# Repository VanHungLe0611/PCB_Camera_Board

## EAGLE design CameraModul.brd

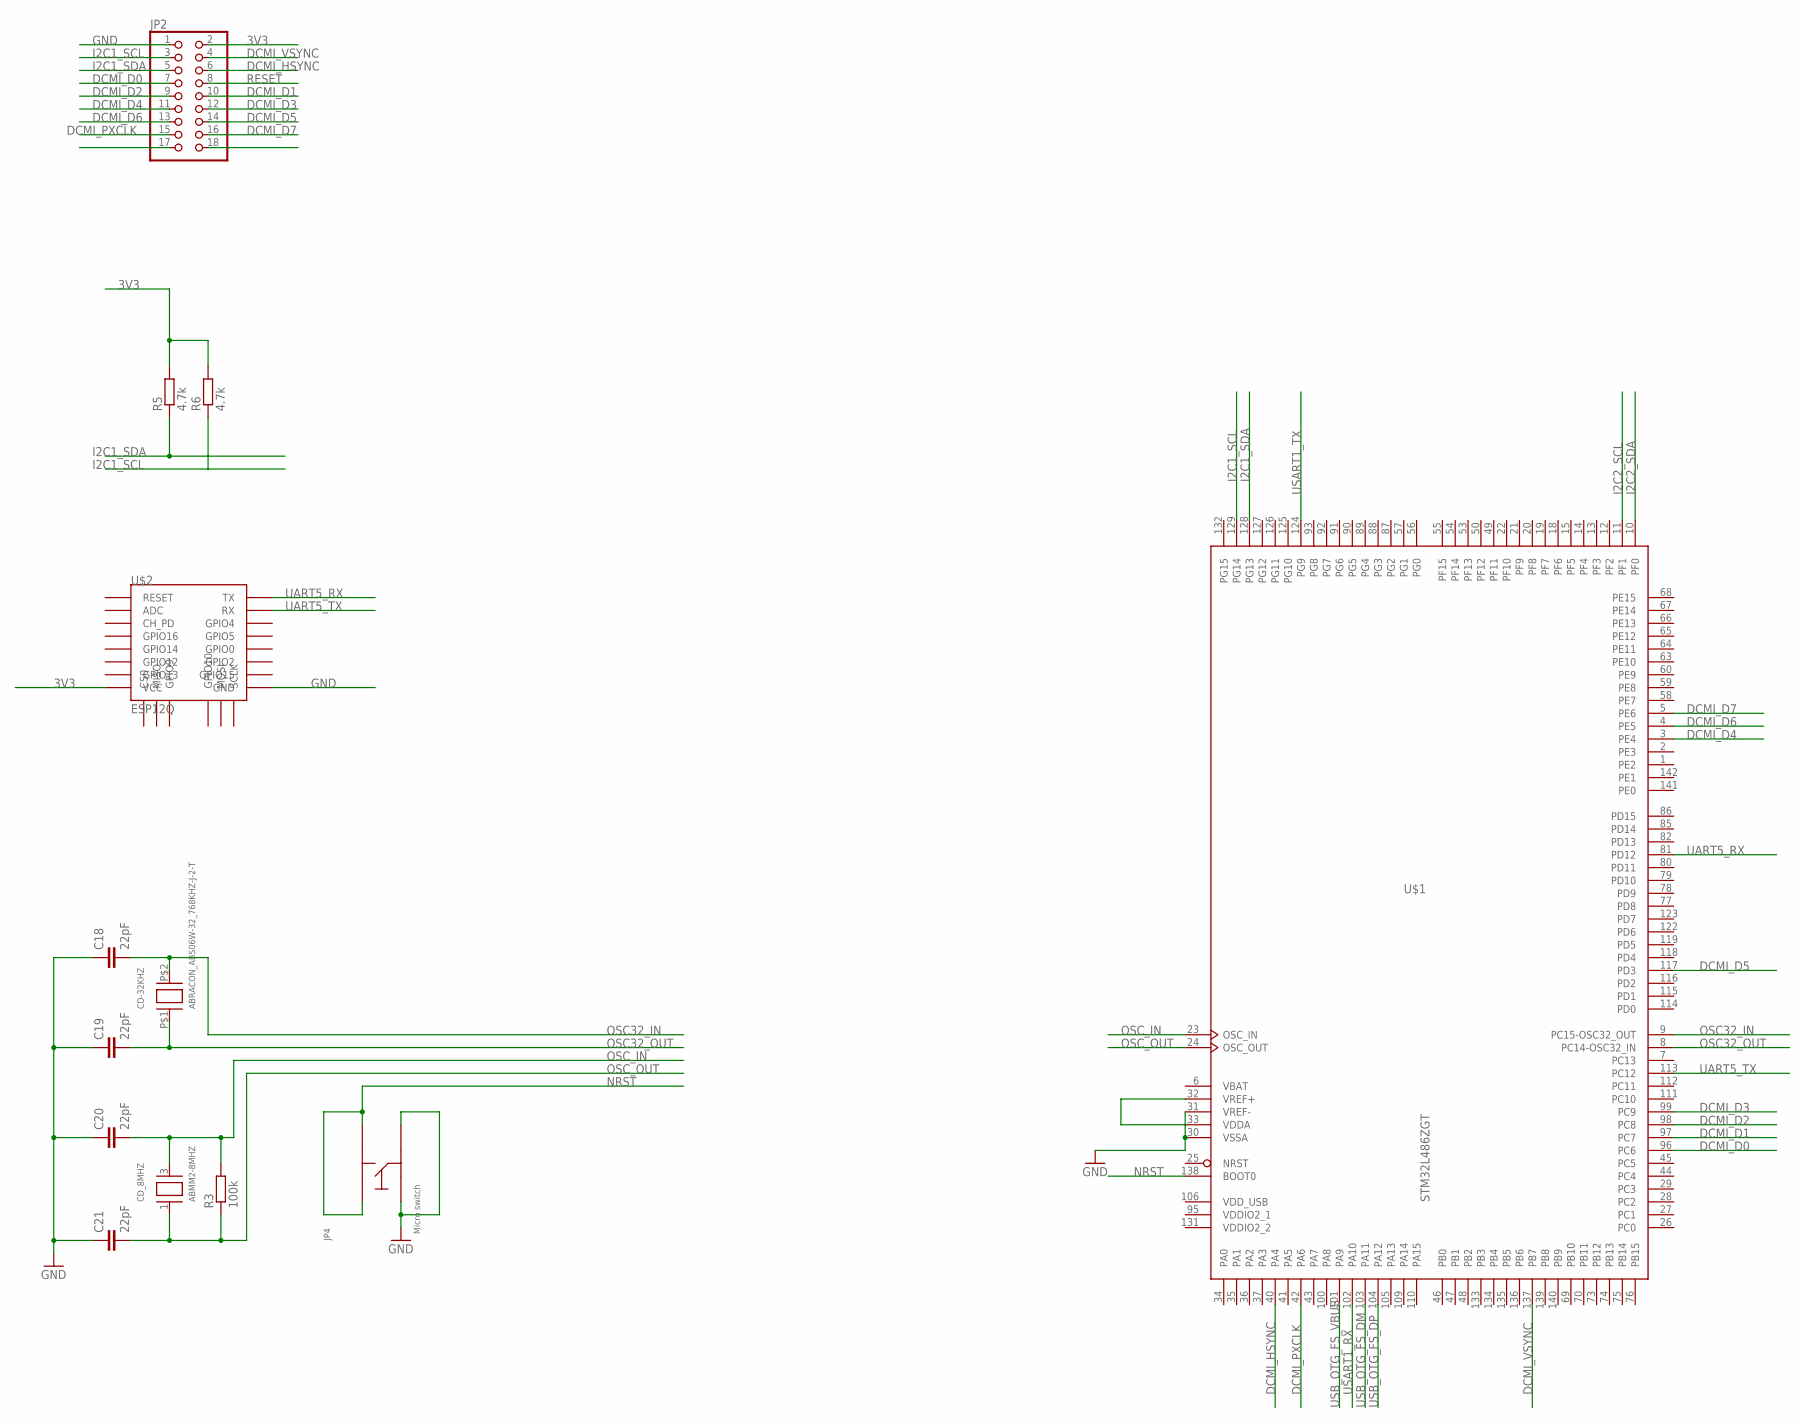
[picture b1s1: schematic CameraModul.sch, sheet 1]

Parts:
C18, C19, C20, C21: 22pF; C0402K
CD-32KHZ: ABRACON_ABS06W-32_768KHZ-J-2-T; 2MM_X_1_2MM
CD_8MHZ: ABMM2-8MHZ; CRYSTAL_ABRACON_6MM_3.6MM
JP2: PINHD-2X9; 2X09
JP4: MICRO_SWITCH_6MM; SKQGADE010
R3: 100k; C0402K
R5, R6: 4.7k; C0402K
U$1: STM32L486ZGT; LQFP144
U$2: ESP12Q

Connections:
3V3: JP2.2, R5.2, R6.2, U$1.32 (VREF+), U$1.33 (VDDA), U$2.VCC; also elsewhere on the board
DCMI_D0: JP2.7, U$1.96 (PC6)
DCMI_D1: JP2.10, U$1.97 (PC7)
DCMI_D2: JP2.9, U$1.98 (PC8)
DCMI_D3: JP2.12, U$1.99 (PC9)
DCMI_D4: JP2.11, U$1.3 (PE4)
DCMI_D5: JP2.14, U$1.117 (PD3)
DCMI_D6: JP2.13, U$1.4 (PE5)
DCMI_D7: JP2.16, U$1.5 (PE6)
DCMI_HSYNC: JP2.6, U$1.40 (PA4)
DCMI_PXCLK: JP2.15, U$1.42 (PA6)
DCMI_VSYNC: JP2.4, U$1.137 (PB7)
GND: C18.1, C19.1, C20.1, C21.1, JP2.1, JP4.P$3, JP4.P$4, U$1.30 (VSSA), U$1.31 (VREF-), U$2.GND; also elsewhere on the board
I2C1_SCL: JP2.3, R6.1, U$1.129 (PG14)
I2C1_SDA: JP2.5, R5.1, U$1.128 (PG13)
I2C2_SCL: U$1.11 (PF1)
I2C2_SDA: U$1.10 (PF0)
NRST: JP4.P$1, JP4.P$2, U$1.138 (BOOT0)
OSC32_IN: C18.2, CD-32KHZ.P$2 (C1), U$1.9 (PC15-OSC32_OUT)
OSC32_OUT: C19.2, CD-32KHZ.P$1 (C0), U$1.8 (PC14-OSC32_IN)
OSC_IN: C20.2, CD_8MHZ.3 (C1), R3.2, U$1.23 (OSC_IN)
OSC_OUT: C21.2, CD_8MHZ.1 (C0), R3.1, U$1.24 (OSC_OUT)
RESET: JP2.8
UART5_RX: U$1.81 (PD12), U$2.TX
UART5_TX: U$1.113 (PC12), U$2.RX
USART1_RX: U$1.102 (PA10); also elsewhere on the board
USART1_TX: U$1.124 (PG9); also elsewhere on the board
USB_OTG_FS_DM: U$1.103 (PA11); also elsewhere on the board
USB_OTG_FS_DP: U$1.104 (PA12); also elsewhere on the board
USB_OTG_FS_VBUS: U$1.101 (PA9); also elsewhere on the board
VBAT: U$1.6 (VBAT); also elsewhere on the board
VDD: U$1.17 (VDD), U$1.39 (VDD), U$1.52 (VDD), U$1.62 (VDD), U$1.72 (VDD), U$1.84 (VDD), U$1.108 (VDD), U$1.121 (VDD), U$1.144 (VDD)
VSS: U$1.16 (VSS), U$1.38 (VSS), U$1.51 (VSS), U$1.61 (VSS), U$1.71 (VSS), U$1.83 (VSS), U$1.94 (VSS), U$1.107 (VSS), U$1.120 (VSS), U$1.130 (VSS), U$1.143 (VSS)

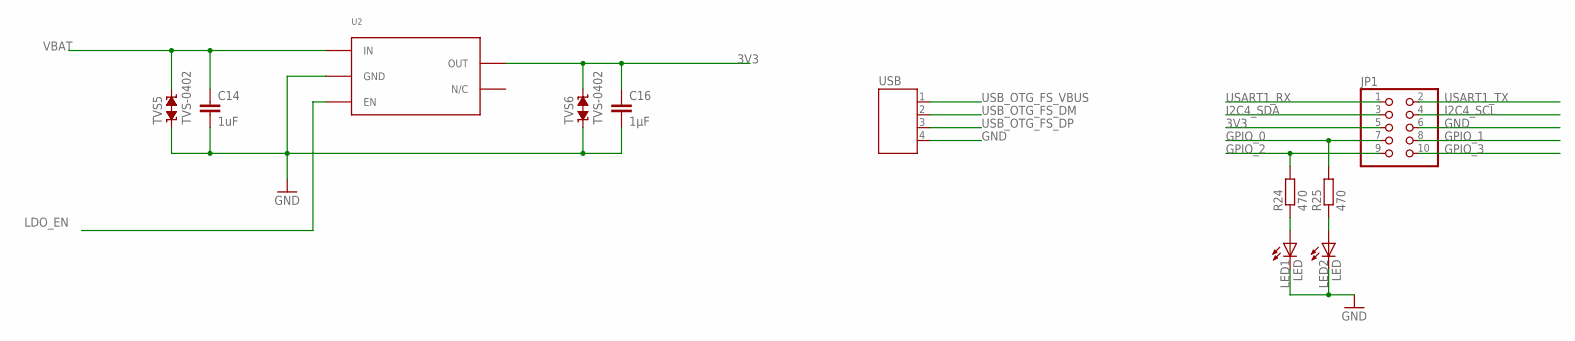
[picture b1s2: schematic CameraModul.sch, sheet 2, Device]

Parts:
C14: 1uF; C0402K
C16: 1µF; C0402K
JP1: PINHD-2X5; 2X05
LED1, LED2: LED; 0603_AK
R24, R25: 470; R0402
TVS5, TVS6: TVS-0402; TVS0402
U2: NCP702; SOT563
USB: JST-PH4

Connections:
3V3: C16.1, JP1.5, TVS6.2, U2.P$5 (OUT); also elsewhere on the board
GND: C14.2, C16.2, JP1.6, LED1.K (C), LED2.K (C), TVS5.1, TVS6.1, U2.P$2 (GND), USB.4; also elsewhere on the board
GPIO_0: JP1.7, R25.2
GPIO_1: JP1.8
GPIO_2: JP1.9, R24.2
GPIO_3: JP1.10
I2C4_SCL: JP1.4
I2C4_SDA: JP1.3
LDO_EN: U2.P$3 (EN)
unnamed: LED1.A, R24.1
unnamed: LED2.A, R25.1
USART1_RX: JP1.1; also elsewhere on the board
USART1_TX: JP1.2; also elsewhere on the board
USB_OTG_FS_DM: USB.2; also elsewhere on the board
USB_OTG_FS_DP: USB.3; also elsewhere on the board
USB_OTG_FS_VBUS: USB.1; also elsewhere on the board
VBAT: C14.1, TVS5.2, U2.P$1 (IN); also elsewhere on the board

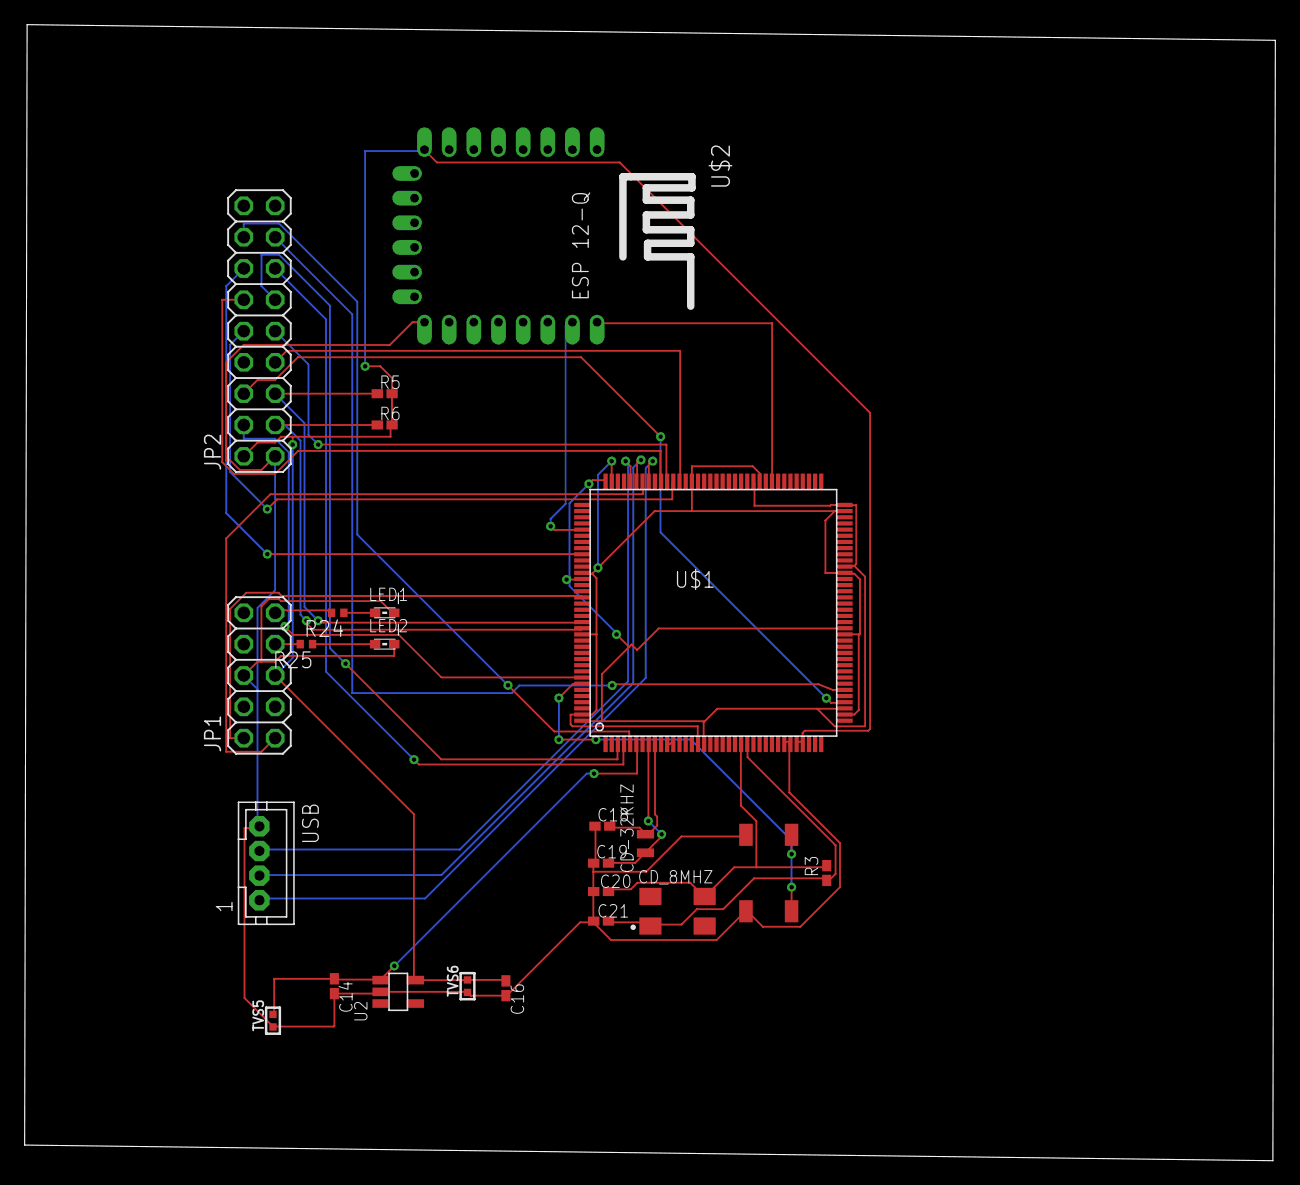
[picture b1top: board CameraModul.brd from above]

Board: 2 copper layers, 101.5 x 92.2 mm, 24 parts (0 on the bottom side), 34 nets.

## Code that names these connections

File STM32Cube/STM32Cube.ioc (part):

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Mcu.Name=STM32L496Z(E-G)Tx
Mcu.Package=LQFP144
Mcu.UserName=STM32L496ZGTx
PA4.Mode=Slave_8_bits_External_Synchro
PA4.Signal=DCMI_HSYNC
PA6.Mode=Slave_8_bits_External_Synchro
PA6.Signal=DCMI_PIXCLK
PB7.Mode=Slave_8_bits_External_Synchro
PB7.Signal=DCMI_VSYNC
PC6.Mode=Slave_8_bits_External_Synchro
PC6.Signal=DCMI_D0
PC7.Mode=Slave_8_bits_External_Synchro
PC7.Signal=DCMI_D1
PC8.Mode=Slave_8_bits_External_Synchro
PC8.Signal=DCMI_D2
PC9.Mode=Slave_8_bits_External_Synchro
PC9.Signal=DCMI_D3
PD3.Mode=Slave_8_bits_External_Synchro
PD3.Signal=DCMI_D5
PE4.Mode=Slave_8_bits_External_Synchro
PE4.Signal=DCMI_D4
PE5.Mode=Slave_8_bits_External_Synchro
PE5.Signal=DCMI_D6
PE6.Mode=Slave_8_bits_External_Synchro
PE6.Signal=DCMI_D7
RCC.HSE_VALUE=8000000
board=custom

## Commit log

2019-08-15 add pcb camera board

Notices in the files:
parts and their libraries:
supressor: Copyright (C) 2009, Bob Starr
